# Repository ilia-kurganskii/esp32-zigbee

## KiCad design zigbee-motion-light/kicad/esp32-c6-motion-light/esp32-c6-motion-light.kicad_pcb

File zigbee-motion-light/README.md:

# Zigbee Motion Light

Motion sensor with LED controller - currently implemented as basic GPIO control.

## Features

- **Motion Detection**: AM312 PIR motion sensor on GPIO 4 with interrupt-driven detection
- **LED Control**: Simple LED on GPIO 5 (on/off control)
- **Auto Control**: LED turns on for 10 seconds when motion detected
- **Build Ready**: Successfully compiles with ESP-IDF

## Hardware Connections

```
AM312 PIR Sensor:
- VCC   -> 3.3V (or 2.7-12V)
- GND   -> GND
- OUT   -> GPIO 4

LED:
- Anode  -> GPIO 5
- Cathode -> GND (with appropriate resistor)
```

## AM312 PIR Sensor Specifications

- **Operating Voltage**: 2.7V - 12V DC
- **Idle Current**: <0.1mA (100µA)
- **Output Delay**: 2 seconds
- **Blocking Time**: 2 seconds
- **Detection Range**: 3-5 meters
- **Field of View**: 100° cone angle
- **Trigger Mode**: Repeatable
- **Operating Temperature**: -20°C to +60°C

The AM312 is an ultra-miniature, low-power PIR sensor ideal for battery-powered applications. It provides a simple digital output (HIGH when motion detected, LOW when no motion).

## Build Instructions

1. Setup ESP-IDF environment:
   ```bash
   source /Users/ilia-kurganskii-air/esp/esp-idf/export.sh
   ```

2. Build and flash:
   ```bash
   cd zigbee-motion-light
   idf.py build
   idf.py -p <PORT> flash monitor
   ```

## Operation

- Motion detected → LED turns on for 10 seconds
- Interrupt-driven motion detection for immediate response
- Basic GPIO implementation ready for Zigbee integration

## Next Steps

This basic version builds successfully. To add Zigbee functionality:

1. Add Zigbee component dependencies back to `idf_component.yml`
2. Restore Zigbee includes and cluster configuration
3. Configure Zigbee settings in `sdkconfig.defaults`
4. Implement Zigbee occupancy and on/off clusters

## Deep sleep & Zigbee rejoin

The device wakes from deep sleep, rejoins the Zigbee network using credentials stored in the `zb_storage` flash partition, sends occupancy, and sleeps again. Typical rejoin time is **~0.7–2 s**.

See **[docs/nvram-rejoin-and-diagnostics.md](docs/nvram-rejoin-and-diagnostics.md)** for:

- NVRAM snapshot log format and how to verify `zb_storage` restore
- Expected serial output after sleep/wake
- Signal handler behavior (`DEVICE_REBOOT` vs steering)
- Flash erase vs firmware-only update

For a clean pairing test:

```bash
idf.py -p <PORT> erase-flash flash monitor
```

## Configuration

Edit `sdkconfig.defaults` for custom settings or use `idf.py menuconfig`.

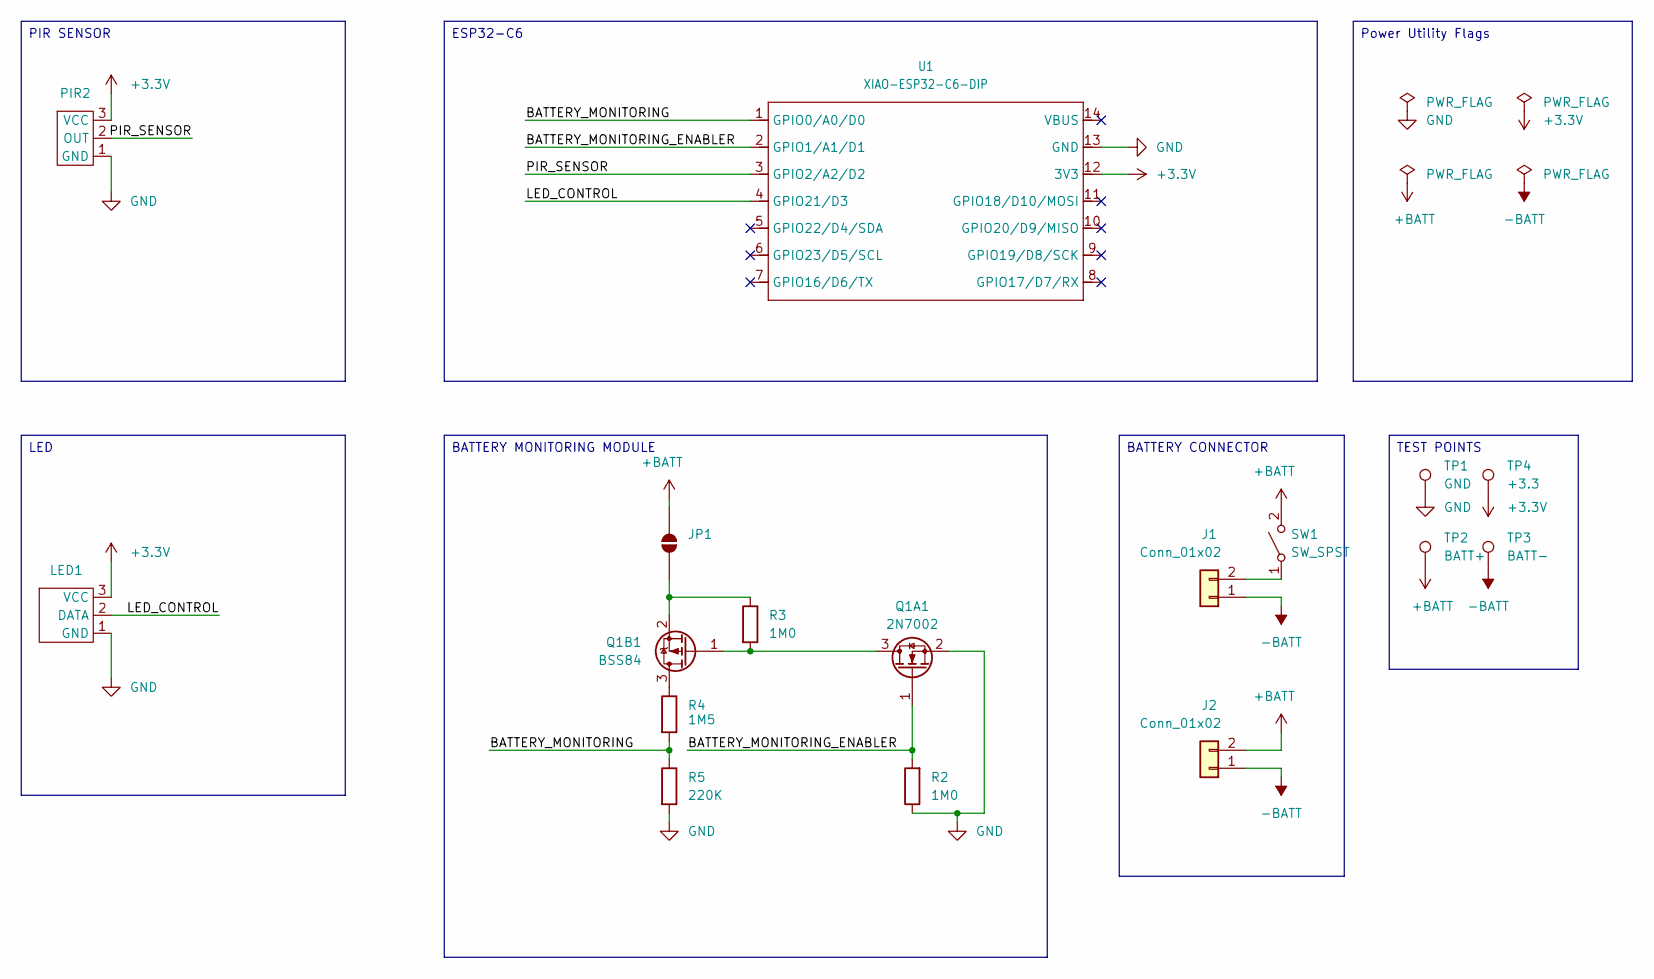
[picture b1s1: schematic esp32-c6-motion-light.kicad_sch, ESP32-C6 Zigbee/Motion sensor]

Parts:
J1, J2: Conn_01x02; JST_XH_B2B-XH-A_1x02_P2.50mm_Vertical
JP1: Enabled for Batter Monitoring; SolderJumper-2_P1.3mm_Open_RoundedPad1.0x1.5mm
LED1: PinHeader_1x03_P2.54mm_Vertical
PIR2: PinHeader_1x03_P2.54mm_Vertical
Q1A1: 2N7002; SOT-23-3_L2.9-W1.3-P1.90-LS2.4-BR
Q1B1: BSS84; SOT-23-3_L3.0-W1.7-P0.95-LS2.9-BR
R2, R3: 1M0; R0805
R4: 1M5; R0603
R5: 220K; R0805
SW1: SW_SPST; PinHeader_1x03_P2.54mm_Vertical
TP1: GND; TestPoint_THTPad_2.0x2.0mm_Drill1.0mm
TP2: BATT+; TestPoint_THTPad_2.0x2.0mm_Drill1.0mm
TP3: BATT-; TestPoint_THTPad_2.0x2.0mm_Drill1.0mm
TP4: +3.3; TestPoint_THTPad_2.0x2.0mm_Drill1.0mm
U1: XIAO-ESP32-C6-DIP; XIAO-ESP32-S3-DIP

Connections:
+3.3V: LED1.3 (VCC), PIR2.3 (VCC), TP4.1 (1_1), U1.12 (3V3); also elsewhere on the board
+BATT: J2.2, JP1.2 (B), SW1.2 (B), TP2.1 (1_1)
-BATT: J1.1, J2.1, TP3.1 (1_1)
/BATTERY_MONITORING: R4.2, R5.1, U1.1 (GPIO0/A0/D0); also elsewhere on the board
/BATTERY_MONITORING_ENABLER: Q1A1.1 (G), R2.2, U1.2 (GPIO1/A1/D1); also elsewhere on the board
/LED_CONTROL: LED1.2 (DATA), U1.4 (GPIO21/D3); also elsewhere on the board
/PIR_SENSOR: PIR2.2 (OUT), U1.3 (GPIO2/A2/D2); also elsewhere on the board
GND: LED1.1 (GND), PIR2.1 (GND), Q1A1.2 (S), R2.1, R5.2, TP1.1 (1_1), U1.13 (GND); also elsewhere on the board
unnamed: J1.2, SW1.1 (A)
unnamed: JP1.1 (A), Q1B1.2 (S), R3.1
unnamed: Q1A1.3 (D), Q1B1.1 (G), R3.2
unnamed: Q1B1.3 (D), R4.1

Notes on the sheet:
LED
TEST POINTS
BATTERY MONITORING MODULE
ESP32-C6
BATTERY CONNECTOR
Power Utility Flags
PIR SENSOR

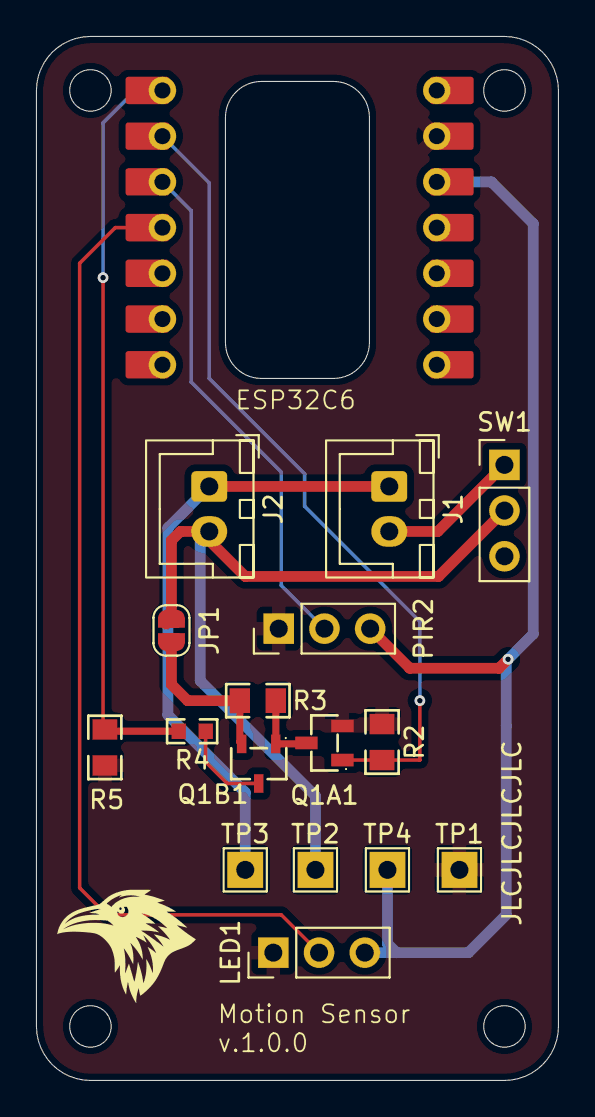
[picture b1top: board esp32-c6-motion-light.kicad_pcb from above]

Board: 4 copper layers, 29.0 x 58.0 mm, 17 parts (0 on the bottom side), 12 nets.

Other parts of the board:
ESP32C6: XIAO-ESP32-C6-DIP; XIAO-ESP32-S3-DIP

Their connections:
+3.3V: ESP32C6.12 (3V3); also elsewhere on the board
/BATTERY_MONITORING: ESP32C6.1 (GPIO0/A0/D0); also elsewhere on the board
/BATTERY_MONITORING_ENABLER: ESP32C6.2 (GPIO1/A1/D1); also elsewhere on the board
/LED_CONTROL: ESP32C6.4 (GPIO21/D3); also elsewhere on the board
/PIR_SENSOR: ESP32C6.3 (GPIO2/A2/D2); also elsewhere on the board
GND: ESP32C6.13 (GND); also elsewhere on the board

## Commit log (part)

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2025-02-22 git init
2025-02-22 feat: somthg work
2025-03-30 fix: fixed
2025-03-30 feat: move to new folder
2025-04-04 feat: add remote
2025-04-09 feat: add base stuff
2025-04-10 feat: implement NVS storage for light driver settings and refactor color handling
2025-06-27 fix: trying multistate
2025-06-27 fix: add correct wtw device
2025-06-27 feat: finally it works
2025-07-20 feat: add documentation
2025-07-20 feat: add ota config (no real)
2025-07-20 feat: refactor modules
2025-07-20 feat: add ai plan
2025-07-20 feat: add project Bootstrap and Build Configuration
2025-07-20 feat: add configuration Management Foundation
2025-07-20 feat: Data Models and Serialization
2025-11-10 feat: it works for serial number
2025-11-10 fix: IT WORKS
2025-11-11 feat: it works even better
2025-11-12 fix: add driver
2025-11-16 feat: add component folder for scd-40
2025-11-16 fix: refactor before zigbee
2025-11-16 feat: add zigbee to config
2025-11-16 feat: update flow
2025-11-16 feat: final fixes
2025-11-29 fix: update gpio for new board
2025-11-29 fix: add power control
2025-11-29 feat: enable 80Mhz to save energy
2025-11-29 fix: fix deep sleep after 60s
2025-12-04 feat: add led signals
2025-12-04 fix: fix issues with 0 measurments
2025-12-14 fix: fix co2 scan
2026-03-30 fix: update I2C GPIO pins and switch to periodic measurement for CO2 sensor
2026-03-30 feat: initialize PCB layout with ESP32-C6 module footprint
2026-03-31 feat: configure PCB stackup and add custom footprint library for 4-layer board
2026-03-31 Add Docker support and fix locale-dependent number formatting
    - Add AGENT.md with development guide for agents
    - Add optimized multi-stage Dockerfile with best practices
    - Fix MemoryHealthIndicator locale issue (use Locale.US for consistent formatting)
    - All tests now pass (49/49 successful)
2026-03-31 Add comprehensive skill development framework and ESP32 project updates
    - Add skill creation framework with validation scripts
    - Add Espressif SDK development skill with references and templates
    - Update zigbee-co2 project with 4MB flash configuration
    - Include project templates and documentation assets
2026-03-31 Add Zigbee build validation workflow
    - Official GitHub Actions only (no third-party dependencies)
    - Validates builds for zigbee-co2, zigbee-light, zigbee-remote, zigbee-wtw
    - ESP32C6 target only (recommended for Zigbee)
    - Smart change detection using git diff
    - 30-minute timeouts to prevent billing issues
    - Triggers on main branch pushes and PRs
2026-03-31 Add OpenAPI documentation with Kotlin OpenAPI Manager skill
    - Add SpringDoc OpenAPI dependency and configuration
    - Implement comprehensive OpenAPI annotations for all controllers
    - Create Kotlin OpenAPI Manager skill with validation and update scripts
    - Add automatic OpenAPI snapshot generation and validation
    - Configure Swagger UI and API documentation endpoints
    - Add health check and metrics controller documentation
2026-03-31 Add Kotlin OpenAPI Manager skill
    - Create comprehensive skill for managing OpenAPI documentation in Kotlin Spring Boot projects
    - Include validation scripts with detailed OpenAPI specification checking
    - Add automatic snapshot update scripts with application management
    - Provide error handling, troubleshooting guidance, and best practices
    - Support for custom ports, automatic detection, and CI/CD integration
    - Include examples, templates, and quality checklists
2026-03-31 Update Espressif SDK skill to focus on build workflow and Windsurf integration
    - Shift focus from project creation to build/flash workflow
    - Add comprehensive Windsurf IDE integration guidance
    - Add metadata section with tags, prerequisites, and platform support
    - Streamline to essential build steps (environment, target, config, build, flash, monitor)
    - Add practical troubleshooting section for common build issues
    - Remove verbose examples and component development details
2026-03-31 Add WiFi connectivity for analytics data transmission
    - Add WiFi initialization and event handling for analytics
    - Add esp_wifi, esp_netif, esp_event dependencies to CMakeLists.txt
    - Implement WiFi connection management with auto-reconnect
    - Add WiFi configuration to sdkconfig.defaults with placeholder credentials
    - Reorder app_main initialization: WiFi before analytics, sensor after Zigbee platform
    - Update flash size configuration to 4MB in sdkconfig.defaults
2026-03-31 Fix shell comparison operators and fetch depth in Zigbee build workflow
    - Change `==` to `=` for POSIX-compliant shell comparisons
    - Increase fetch-depth from 2 to 0 for complete git history access
    - Apply changes consistently across all four Zigbee project jobs (co2, light, remote, wtw)
2026-03-31 Fix git diff comparison in Zigbee build workflow for pull requests
    - Add explicit base branch fetch step for PR events
    - Change git diff from `origin/${{ github.base_ref }}` to `${{ github.base_ref }}` for reliable local comparison
    - Apply changes consistently across all four Zigbee project jobs (co2, light, remote, wtw)
    - Ensure proper branch reference resolution in change detection steps
2026-04-14 fix: revert I2C GPIO pins to 6/7 and update SDK configuration settings
    - Revert I2C pins from GPIO 23/22 back to GPIO 6/7 for SCL/SDA
    - Update SDK version from 6.1.0 to 5.5.1
    - Switch compiler optimization from performance to debug mode
    - Change CPU frequency from 80MHz to 160MHz
    - Update IEEE802154 CCA threshold from -75 to -60
    - Disable bootloader deep sleep validation
2026-04-17 Update LED driver and simplify for testing
    - Copy LED driver from zigbee-light (RGB LED strip support)
    - Remove NVS storage from LED driver (use in-memory only)
    - Add logging to LED driver functions
    - Change LED GPIO to 21 and LED count to 3
    - Simplify main.c to LED blinking test
    - Comment out Zigbee and motion sensor code
2026-04-17 Update motion sensor GPIO and add AM312 PIR specifications
    - Change motion sensor GPIO from 4 to 17
    - Add AM312 PIR sensor specifications and documentation
    - Update README with detailed AM312 sensor specs and wiring
    - Add LED GPIO pin comment (D3)
    - Change LED test from blinking to RGB color cycling
    - Set LED brightness to 1% (2/255) for testing
2026-04-17 Change motion sensor GPIO from 17 to 20 and add motion detection test
    - Update motion sensor GPIO from 17 to 20 (D9 pin)
    - Replace LED color cycling test with AM312 motion detection test
    - Add motion_driver.h include and initialize motion driver
    - Change main loop to detect and log motion events every 100ms
    - Update TAG from "LED_TEST" to "MOTION_LIGHT"
    - Update KiCad submodule state to dirty
2026-04-17 fix(motion-light): configure GPIO wakeup for deep sleep compatibility
    Changed GPIO wakeup from edge mode (POSEDGE) to level mode (HIGH_LEVEL) as ESP32 deep sleep only supports level triggers. Removed ISR installation since deep sleep uses GPIO wakeup directly. Added 10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
2026-04-17 fix(motion-light): change motion sensor to LP GPIO 2 and update deep sleep wakeup API
    - Change motion sensor GPIO from 20 to 2 (LP GPIO for deep sleep wakeup)
    - Switch from pull-down to pull-up resistor configuration
    - Replace deprecated esp_sleep_enable_gpio_wakeup() with esp_deep_sleep_enable_gpio_wakeup()
    - Simplify wakeup configuration to single API call with bitmask
    - Reduce debug loop iterations from 20 to 10
    - Update KiCad submodule state to dirty
2026-04-19 feat(motion-light): add LED status indicators for wakeup reasons and motion detection
    - Initialize LED driver on startup and turn on power
    - Set LED to green when woken by motion detection
    - Set LED to red for timer wakeup or normal boot
    - Turn off LED before entering deep sleep
    - Update KiCad submodule state to dirty
2026-04-19 feat(motion-light): add LED bounce animation for wakeup indication
    - Add light_driver_set_pixel() function to control individual LEDs
    - Remove verbose logging from light_driver_set_rgb()
    - Replace debug loop with LED bounce animation (20 rounds)
    - Set LED color based on wakeup reason (green for GPIO, red for timer/boot)
    - Add 10-second delay before sleep only for non-GPIO wakeup
    - Keep first LED active after animation completes
2026-05-01 feat(motion-light): add time-based scheduling with Zigbee time sync and increase LED count
    - Increase LED strip from 3 to 20 LEDs
    - Add time_schedule component with NVS-backed configuration
    - Implement Zigbee Time Cluster integration for UTC time sync
    - Add RTC memory persistence for time sync state across deep sleep
    - Add configurable active hours (default 22:00-06:00) with timezone support
    - Implement periodic time resync every 6 hours
2026-05-01 fix(motion-light): use single LED only for battery efficiency
    Replace all light_driver_set_rgb() calls with light_driver_set_pixel(0, r, g, b)
    to ensure only LED 0 is lit for status indicators, preventing all 20 LEDs
    from draining battery simultaneously.
    Changes:
    - Change default RGB from white to black in light_driver.c to prevent
    white flash on init
2026-05-02 feat(motion-light): improve time sync persistence and LED animation responsiveness
    - Increase LED strip from 20 to 65 LEDs
    - Move timezone offset from RTC to NVS for power cycle persistence
    - Add time sync status to NVS (persists across power cycles)
    - Change LED animation to non-blocking: start Zigbee sync in background
    - Remove 30-second blocking wait for time sync
    - Update LED colors: motion = warm amber (255,180,0), sync = blue flash
2026-05-02 Refactor Zigbee code into separate component
    - Create zigbee_motion component with header, source, and CMakeLists
    - Move Zigbee initialization, callbacks, and occupancy reporting to component
    - Update main.c to use zigbee_motion component API
    - Simplify main.c from 350+ lines to ~220 lines
    - Add zigbee_motion dependency to main component
    - Build verified successfully
2026-05-03 Add KiCAD design for ESP32-C6 motion light
    - Add ESP32-C6 motion light PCB design
    - Include schematic, PCB layout, and project files
    - Add .gitignore for KiCAD backups and history
    - Design supports AM312 PIR sensor and LED strip
2026-05-03 Update zigbee-co2 KiCAD library and design files
2026-05-03 Remove .history from zigbee-co2 kicad and add .gitignore
2026-05-03 Add shared KiCAD libraries (custom and seeed_studio)
2026-05-03 Add architecture documentation for zigbee-motion-light
2026-05-05 Add RP2040 component from EasyEDA and update KiCad project files
2026-05-08 Remove unused custom KiCAD footprints (SCD41-4pins and XIAO-ESP32-C6-DIP)
2026-05-08 Remove all time-related code from codebase
    - Remove time_schedule component entirely
    - Remove time sync logic from zigbee_motion component
    - Remove Time cluster from Zigbee configuration
    - Remove time schedule checks from main application
    - Simplify animation logic (always animate on GPIO wake)
    - Update architecture documentation
2026-05-08 feat: fix iss
2026-05-10 feat: update kikad
2026-05-11 fix: wait for Zigbee join before deep sleep and fix task lifecycle
